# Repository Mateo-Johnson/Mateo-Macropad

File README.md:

# RP2040 Macro Pad

Compact 8-key macro pad built around the XIAO RP2040 DIP module. Features per-key RGB backlighting using SK6812MINI LEDs, a minimal PCB, and a custom 3D-printed enclosure.

---

## Features
- 8× MX-style mechanical switches  
- 3× SK6812MINI addressable RGB LEDs  
- XIAO RP2040 microcontroller  
- Custom PCB with direct switch routing  
- Lightweight printed case with USB-C access

---

## Hardware Overview
### Microcontroller  
- Seeed Studio XIAO RP2040 (DIP package)

### Layout  
- Switches arranged in a compact 2×4 configuration  
- RGB LEDs daisy-chained: DIN → DOUT path across the PCB  
- USB-C through the case opening for programming and power

### Case  
- Two-piece shell designed for friction-fit or fastener-based closure  
- Plate openings sized for MX-compatible housings  
- Internal clearance for the XIAO and LEDs

---

## Bill of Materials (BOM)
| Quantity | Item |
|---------|------|
| 1 | XIAO RP2040 (DIP) |
| 8 | MX-style switches |
| 3 | SK6812MINI RGB LEDs |
| — | Printed case components |
| — | USB-C cable |

---

## Project Images
**Overall Build**  

**Schematic**  

**PCB Layout**  

**Case**  

---

## Firmware
Compatible with CircuitPython, MicroPython, or a custom C++/Pico-SDK firmware. QMK support is possible with additional configuration.

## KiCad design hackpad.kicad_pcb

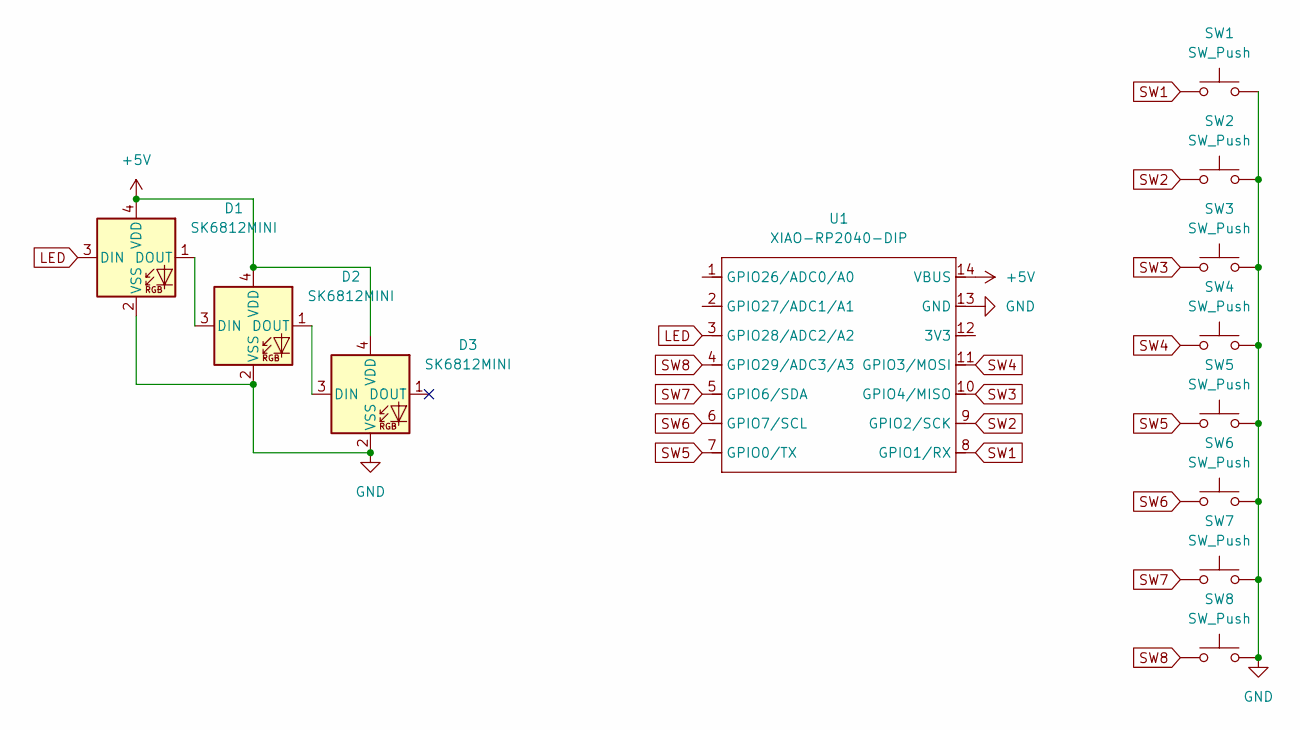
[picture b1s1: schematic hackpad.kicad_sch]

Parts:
D1, D2, D3: SK6812MINI; LED_SK6812MINI_PLCC4_3.5x3.5mm_P1.75mm
SW1, SW2, SW3, SW4, SW5, SW6, SW7, SW8: SW_Push; SW_Cherry_MX_1.00u_PCB
U1: XIAO-RP2040-DIP

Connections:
+5V: D1.4 (VDD), D2.4 (VDD), D3.4 (VDD), U1.14 (VBUS)
GND: D1.2 (VSS), D2.2 (VSS), D3.2 (VSS), SW1.2, SW2.2, SW3.2, SW4.2, SW5.2, SW6.2, SW7.2, SW8.2, U1.13 (GND)
LED: D1.3 (DIN), U1.3 (GPIO28/ADC2/A2)
unnamed: D1.1 (DOUT), D2.3 (DIN)
unnamed: D2.1 (DOUT), D3.3 (DIN)
SW1: SW1.1, U1.8 (GPIO1/RX)
SW2: SW2.1, U1.9 (GPIO2/SCK)
SW3: SW3.1, U1.10 (GPIO4/MISO)
SW4: SW4.1, U1.11 (GPIO3/MOSI)
SW5: SW5.1, U1.7 (GPIO0/TX)
SW6: SW6.1, U1.6 (GPIO7/SCL)
SW7: SW7.1, U1.5 (GPIO6/SDA)
SW8: SW8.1, U1.4 (GPIO29/ADC3/A3)

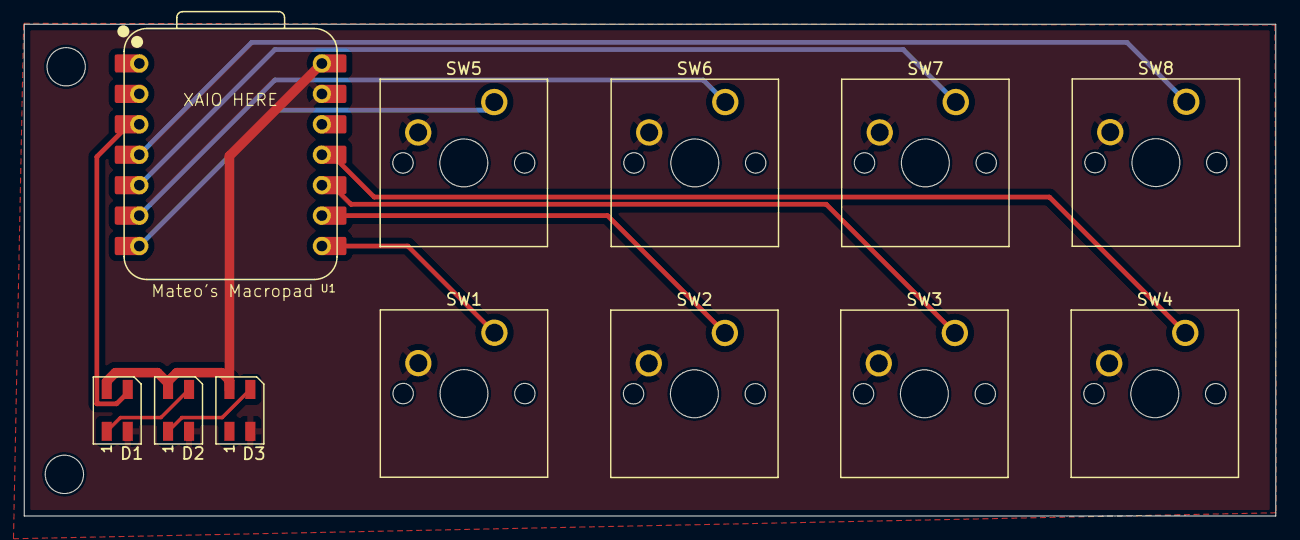
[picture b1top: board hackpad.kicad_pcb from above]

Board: 2 copper layers, 104.5 x 41.0 mm, 14 parts (0 on the bottom side), 13 nets.

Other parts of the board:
H1, H2: MountingHole; MountingHole_3.2mm_M3

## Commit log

2025-11-27 upload CAD file
2025-11-27 Rename Mateo's Macropad.step to CAD/Mateo's Macropad.step
2025-11-27 Rename hackpad.kicad_pcb to PCB/hackpad.kicad_pcb
2025-11-27 Rename hackpad.kicad_pro to PCB/hackpad.kicad_pro
2025-11-27 Rename hackpad.kicad_sch to PCB/hackpad.kicad_sch
2025-11-27 Revise README with project details and images
    Updated README to include project features, hardware overview, and bill of materials.
